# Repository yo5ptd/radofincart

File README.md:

Radofin 1392 cartridge for 27128 ROM
If you just need a quick way to test a retro video computer

Supports 8 games in a single cartridge of size 2Kbytes or 4 games of 4Kbytes.

Use only 2K or 4K roms in a single ROM.

Use 27128 ROMS.

6 pin ic is actually a 3 pin DIP switch. For 4k ROM cartridge you can use 2 pin DIP switch.

11.01.2025:
added STL files for 3d printed case. You need to drill holes on the PCB.

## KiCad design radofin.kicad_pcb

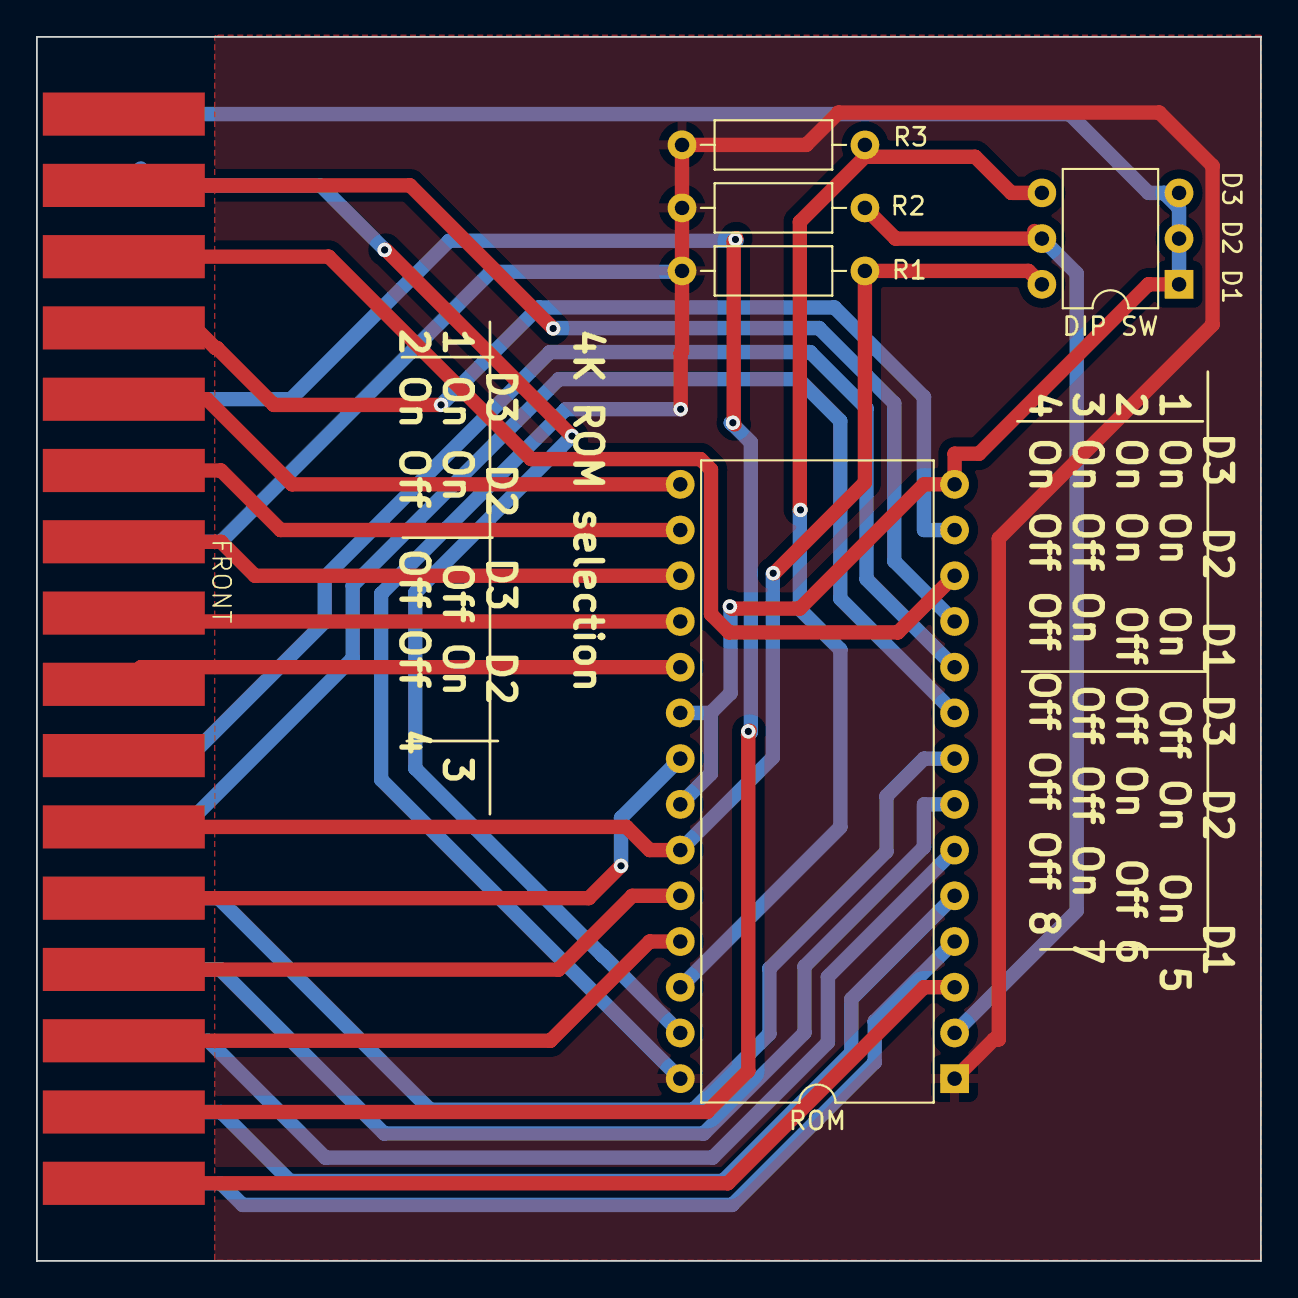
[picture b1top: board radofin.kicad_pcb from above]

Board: 2 copper layers, 68.0 x 68.0 mm, 6 parts (0 on the bottom side), 26 nets.

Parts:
DIP SW: SW_DIP_x03; DIP-6_W7.62mm
FRONT: Conn_02x16_Counter_Clockwise; radofin
R1, R2, R3: 10k; R_Axial_DIN0207_L6.3mm_D2.5mm_P10.16mm_Horizontal
ROM: 27C128; DIP-28_W15.24mm

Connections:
/A0: FRONT.26, ROM.10 (A0)
/A1: FRONT.27, ROM.9 (A1)
/A2: FRONT.28, ROM.8 (A2)
/A3: FRONT.29, ROM.7 (A3)
/A4: FRONT.30, ROM.6 (A4)
/A5: FRONT.31, ROM.5 (A5)
/A6: FRONT.32, ROM.4 (A6)
/A7: FRONT.1, ROM.3 (A7)
/A8: FRONT.3, ROM.25 (A8)
/A9: FRONT.4, ROM.24 (A9)
/A10: FRONT.5, ROM.21 (A10)
/A11: DIP SW.6, FRONT.6, R1.1, ROM.23 (A11)
/A12: DIP SW.5, R2.1, ROM.2 (A12)
/A13: DIP SW.4, R3.1, ROM.26 (A13)
/D0: FRONT.15, ROM.11 (D0)
/D1: FRONT.14, ROM.12 (D1)
/D2: FRONT.13, ROM.13 (D2)
/D3: FRONT.12, ROM.15 (D3)
/D4: FRONT.11, ROM.16 (D4)
/D5: FRONT.10, ROM.17 (D5)
/D6: FRONT.9, ROM.18 (D6)
/D7: FRONT.8, ROM.19 (D7)
//PGM: FRONT.18, ROM.27 (~PGM)
GND: DIP SW.1, DIP SW.2, DIP SW.3, FRONT.17, ROM.14 (GND), ROM.20 (~CE), ROM.22 (~OE)
unnamed: FRONT.2, FRONT.21
VCC: FRONT.23, R1.2, R2.2, R3.2, ROM.1 (VPP), ROM.28 (VCC)

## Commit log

2024-03-04 Rewiring after an optical review
2024-03-04 Photos
2025-01-11 3d printed case
